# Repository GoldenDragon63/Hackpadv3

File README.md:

* Keyboard Maintainer: [Goldendragon63]
* Hardware Supported: The PCBs, controllers supported
* Hardware Availability:Links to where you can find this hardware

Make example for this keyboard (after setting up your build environment):

    make planck/rev4:default

Flashing example for this keyboard:

    make planck/rev4:default:flash

See the [build environment setup](getting_started_build_tools) and the [make instructions](getting_started_make_guide) for more information. Brand new to QMK? Start with our [Complete Newbs Guide](newbs).

## Bootloader

Enter the bootloader in 3 ways:

* **Bootmagic reset**: Hold down the key at (0,0) in the matrix (usually the top left key or Escape) and plug in the keyboard
* **Physical reset button**: Briefly press the button on the back of the PCB - some may have pads you must short instead
* **Keycode in layout**: Press the key mapped to `QK_BOOT` if it is available

## BOM
* Seeed XIAO RP2040
* 10 MX-Style switches
* 10 Blank DSA Keycaps
* 10 Diode_THT:D_DO-35_SOD27_P7.62mm_Horizontal
* 5 LED_SMD:LED_WS2812B_PLCC4_5.0x5.0mm_P3.2mm
* 1 0.91 inch OLED display with pin order GND-VCC-SCL-SDA
* 1 3D-printed case (two seperate parts)
* 4 Screws M3

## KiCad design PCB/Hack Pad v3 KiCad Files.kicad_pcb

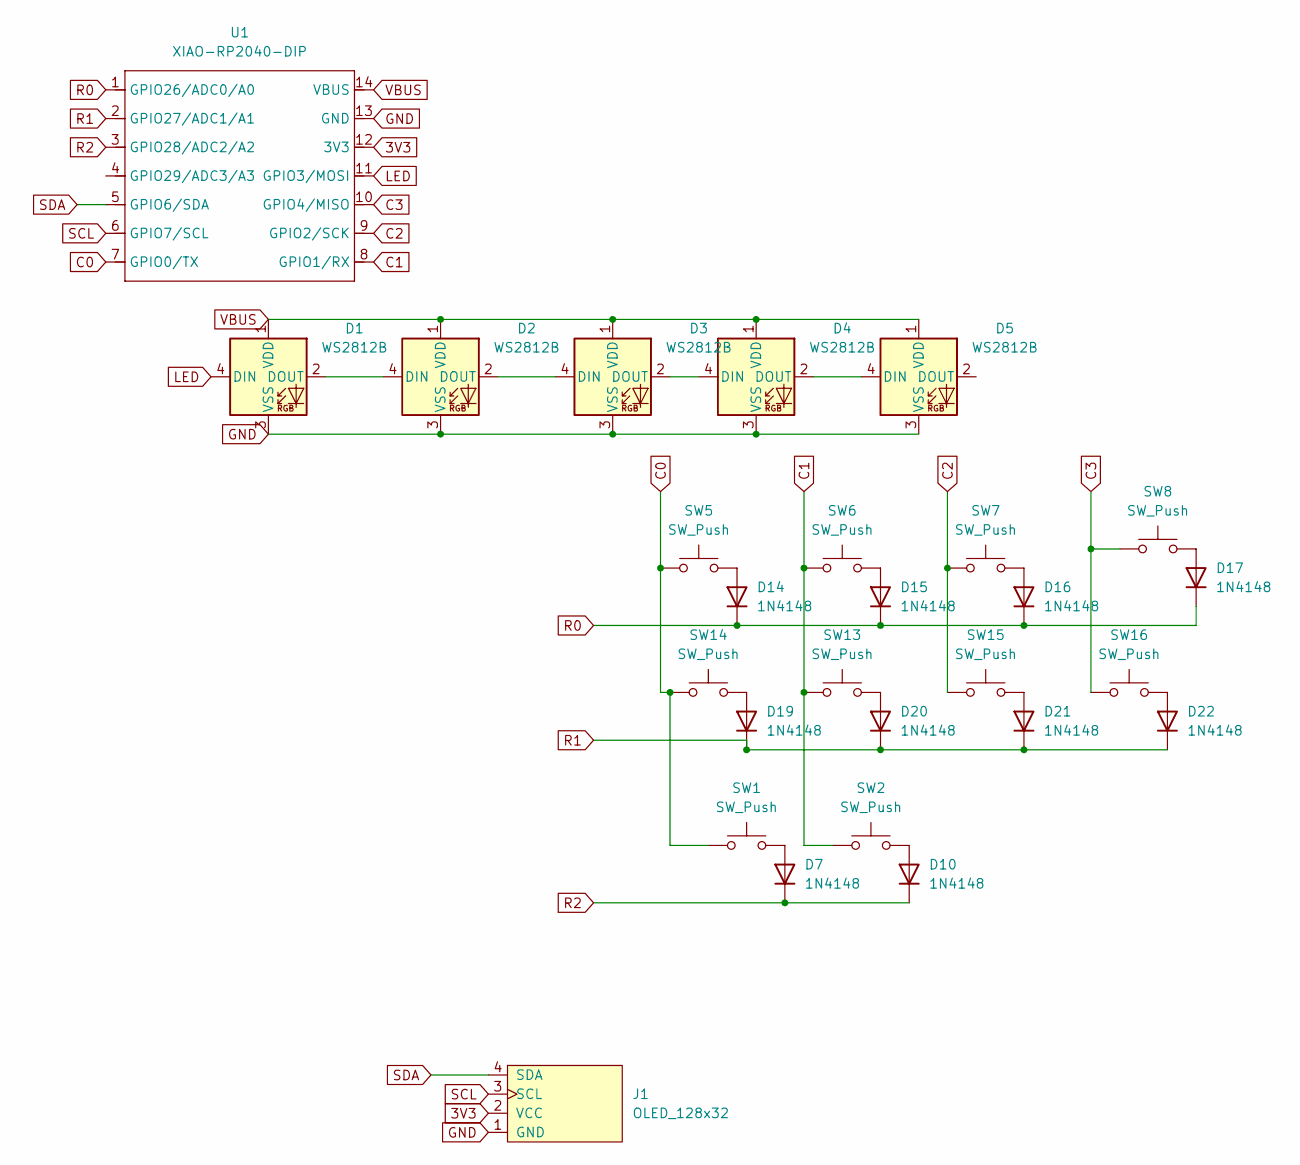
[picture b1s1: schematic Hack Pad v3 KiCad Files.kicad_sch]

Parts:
D1, D2, D3, D4, D5: WS2812B; LED_WS2812B_PLCC4_5.0x5.0mm_P3.2mm
D7, D10, D14, D15, D16, D17, D19, D20, D21, D22: 1N4148; D_DO-35_SOD27_P7.62mm_Horizontal
J1: OLED_128x32
SW1, SW2, SW5, SW6, SW7, SW8, SW13, SW14, SW15, SW16: SW_Push; SW_Cherry_MX_1.00u_PCB
U1: XIAO-RP2040-DIP; XIAO-RP2040-SMD

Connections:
3V3: J1.2 (VCC), U1.12 (3V3)
C0: SW1.1, SW5.1, SW14.1, U1.7 (GPIO0/TX)
C1: SW2.1, SW6.1, SW13.1, U1.8 (GPIO1/RX)
C2: SW7.1, SW15.1, U1.9 (GPIO2/SCK)
C3: SW8.1, SW16.1, U1.10 (GPIO4/MISO)
GND: D1.3 (VSS), D2.3 (VSS), D3.3 (VSS), D4.3 (VSS), D5.3 (VSS), J1.1 (GND), U1.13 (GND)
LED: D1.4 (DIN), U1.11 (GPIO3/MOSI)
unnamed: D1.2 (DOUT), D2.4 (DIN)
unnamed: D2.2 (DOUT), D3.4 (DIN)
unnamed: D3.2 (DOUT), D4.4 (DIN)
unnamed: D4.2 (DOUT), D5.4 (DIN)
unnamed: D7.2 (A), SW1.2
unnamed: D10.2 (A), SW2.2
unnamed: D14.2 (A), SW5.2
unnamed: D15.2 (A), SW6.2
unnamed: D16.2 (A), SW7.2
unnamed: D17.2 (A), SW8.2
unnamed: D19.2 (A), SW14.2
unnamed: D20.2 (A), SW13.2
unnamed: D21.2 (A), SW15.2
unnamed: D22.2 (A), SW16.2
R0: D14.1 (K), D15.1 (K), D16.1 (K), D17.1 (K), U1.1 (GPIO26/ADC0/A0)
R1: D19.1 (K), D20.1 (K), D21.1 (K), D22.1 (K), U1.2 (GPIO27/ADC1/A1)
R2: D7.1 (K), D10.1 (K), U1.3 (GPIO28/ADC2/A2)
SCL: J1.3 (SCL), U1.6 (GPIO7/SCL)
SDA: J1.4 (SDA), U1.5 (GPIO6/SDA)
VBUS: D1.1 (VDD), D2.1 (VDD), D3.1 (VDD), D4.1 (VDD), D5.1 (VDD), U1.14 (VBUS)

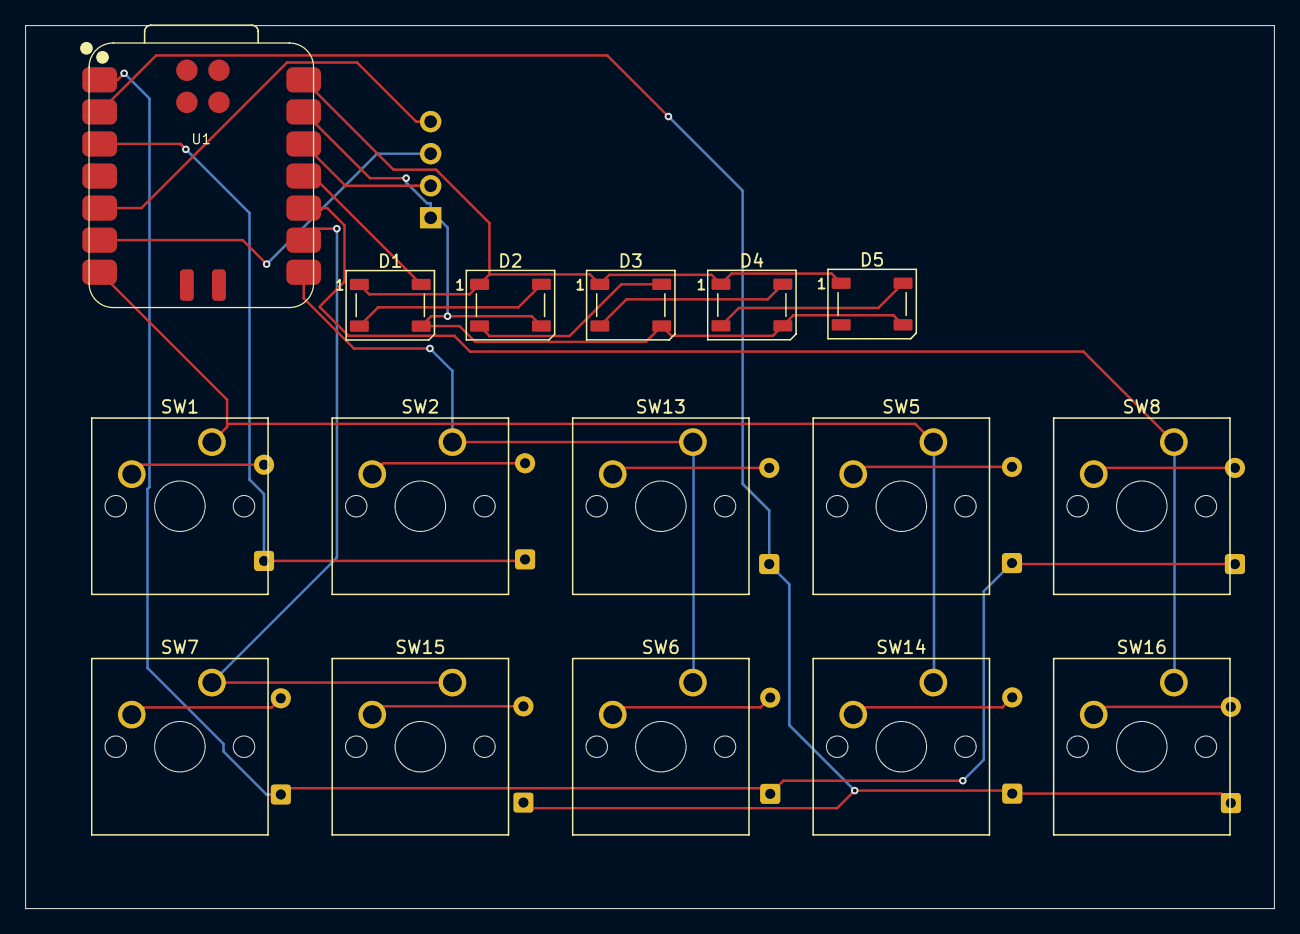
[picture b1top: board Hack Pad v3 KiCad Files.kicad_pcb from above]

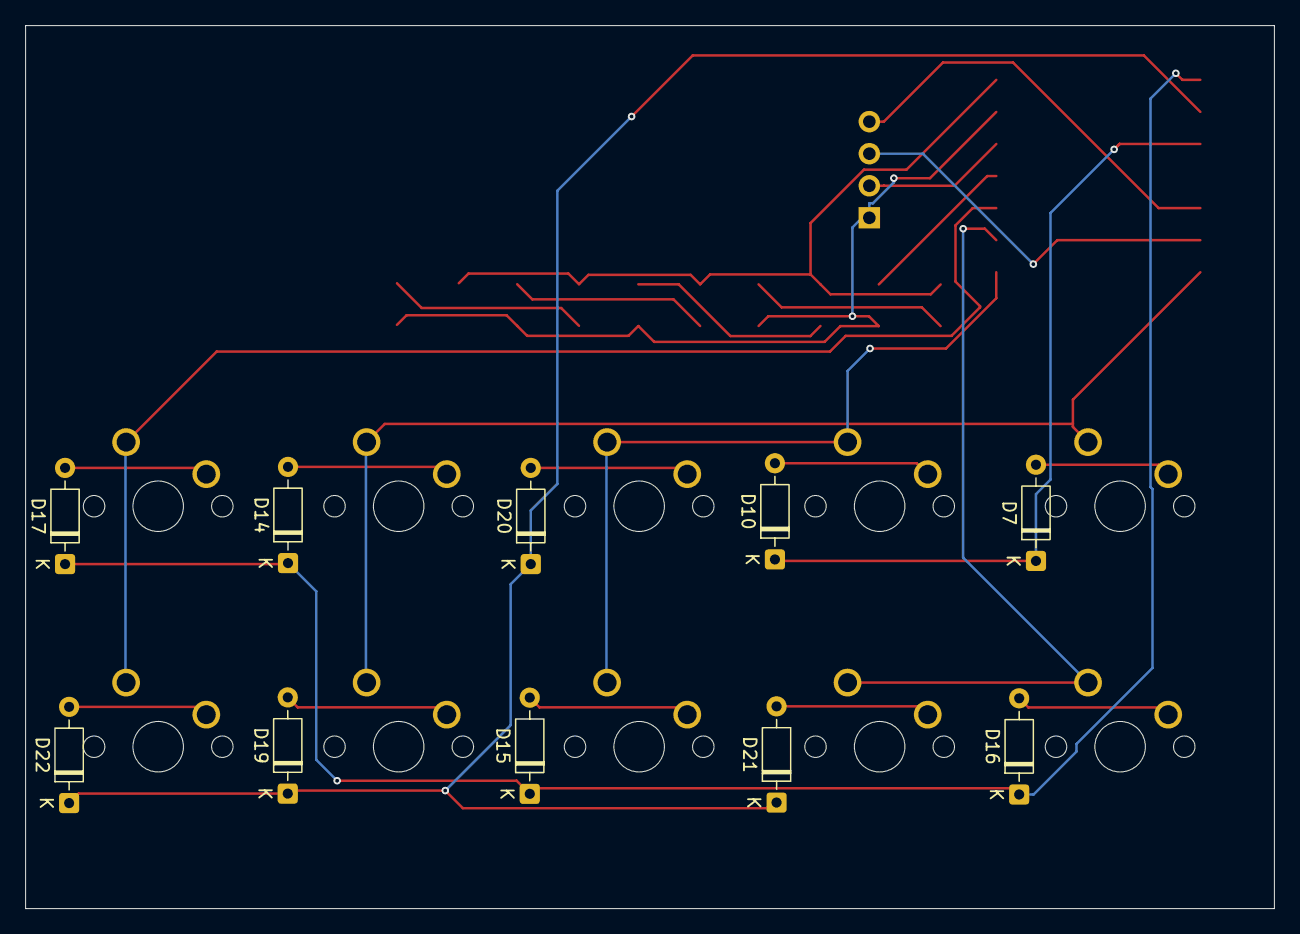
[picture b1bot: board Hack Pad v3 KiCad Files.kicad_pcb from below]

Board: 2 copper layers, 98.9 x 70.0 mm, 27 parts (10 on the bottom side), 27 nets.

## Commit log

2025-07-03 PCB Files
2025-07-03 CAD Files
2025-07-05 Production Files
2025-07-06 Uploaded Production Files
2025-07-06 Uploaded Firmware
2025-07-09 Updated CAD Files
2025-07-09 Updated CAD
2025-07-10 PCB Case
